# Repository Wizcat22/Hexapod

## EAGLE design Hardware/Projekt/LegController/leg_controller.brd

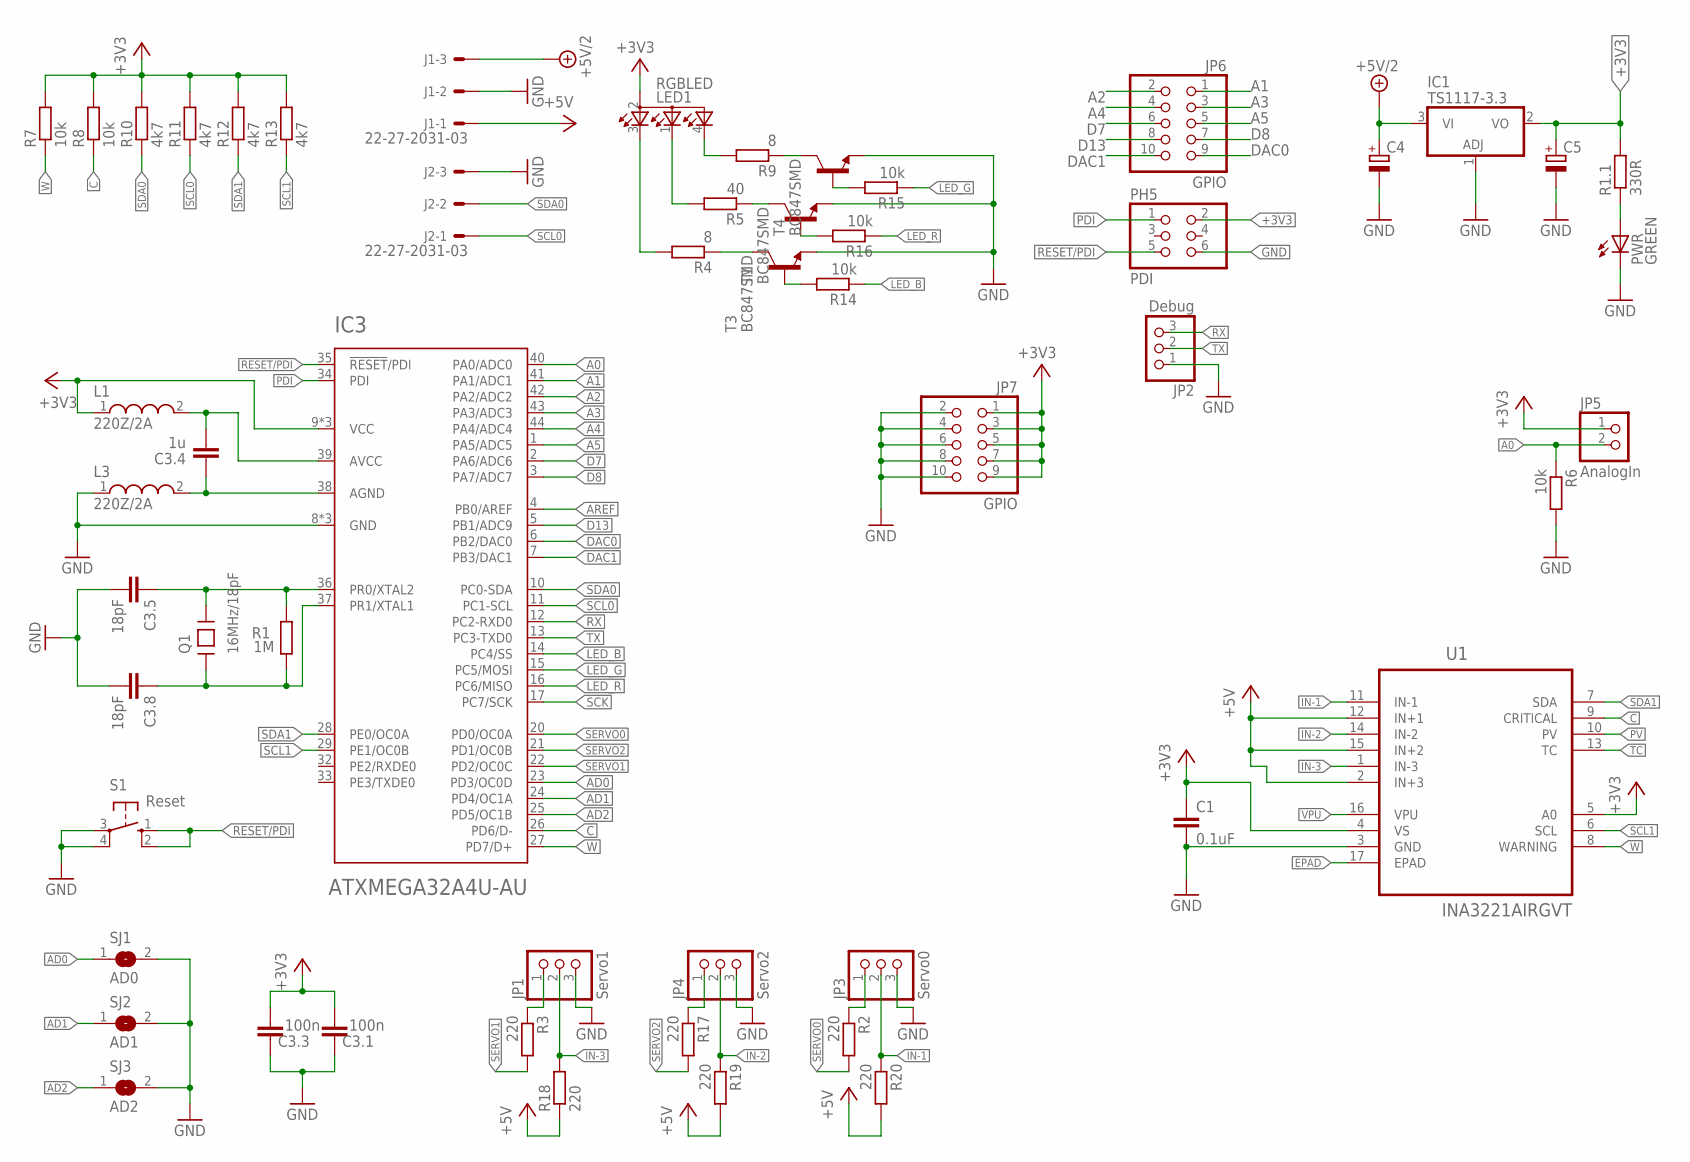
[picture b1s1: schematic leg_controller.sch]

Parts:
C1: 0.1uF; C0805
C3.1, C3.3: 100n; C0805K
C3.4: 1u; C0805K
C3.5, C3.8: 18pF; C0805K
C4, C5: CPOL-EUSMCA; SMC_A
IC1: TS1117-3.3; DPACK
IC3: ATXMEGA32A4U-AU; TQFP-44A-44
J1, J2: 22-27-2031-03; 6410-03
JP1: Servo1; 1X03
JP2: Debug; 1X03
JP3: Servo0; 1X03
JP4: Servo2; 1X03
JP5: AnalogIn; 1X02
JP6, JP7: GPIO; 2X05
L1, L3: 220Z/2A; WE-CBF_0805(W=3.0)
LED1: RGBLED; P-LCC4-RGB
PH5: PDI; 2X03
PWR: GREEN; CHIP-LED0805
Q1: 16MHz/18pF; CRYSTAL-ABRACON-ABM3-SMD
R1: 1M; R0805
R1.1: 330R; R0805
R2, R3, R17: 220; R0805
R4, R9: 8; R0805
R5: 40; R0805
R6: 10k; M0805
R7, R8, R14, R15, R16: 10k; R0805
R10, R11, R12, R13: 4k7; R0805
R18, R19, R20: 220; R1206
S1: Reset; B3F-10XX
SJ1: AD0; SJ
SJ2: AD1; SJ
SJ3: AD2; SJ
T1, T3, T4: BC847SMD; SOT23
U1: INA3221AIRGVT; QFN65P400X400X80-17N

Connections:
+3V3: C1.1, C3.1.1, C3.3.1, C5.+, IC1.2 (VO), IC3.9 (VCC), IC3.19 (VCC), IC3.31 (VCC), JP5.1, JP7.1, JP7.3, JP7.5, JP7.7, JP7.9, L1.1, LED1.2 (A2), PH5.2, R1.1.2, R7.2, R8.2, R10.2, R11.2, R12.2, R13.2, U1.4 (VS), U1.5 (A0)
+5V: J1.1, R18.1, R19.2, R20.2, U1.2 (IN+3), U1.12 (IN+1), U1.15 (IN+2)
+5V/2: C4.+, IC1.3 (VI), J1.3
A0: IC3.40 (PA0/ADC0), JP5.2, R6.1
A1: IC3.41 (PA1/ADC1), JP6.1
A2: IC3.42 (PA2/ADC2), JP6.2
A3: IC3.43 (PA3/ADC3), JP6.3
A4: IC3.44 (PA4/ADC4), JP6.4
A5: IC3.1 (PA5/ADC5), JP6.5
AD0: IC3.23 (PD3/OC0D), SJ1.1
AD1: IC3.24 (PD4/OC1A), SJ2.1
AD2: IC3.25 (PD5/OC1B), SJ3.1
AGND: C3.4.2, IC3.38 (AGND), L3.2
AREF: IC3.4 (PB0/AREF)
C: IC3.26 (PD6/D-), R8.1, U1.9 (CRITICAL)
D7: IC3.2 (PA6/ADC6), JP6.6
D8: IC3.3 (PA7/ADC7), JP6.7
D13: IC3.5 (PB1/ADC9), JP6.8
DAC0: IC3.6 (PB2/DAC0), JP6.9
DAC1: IC3.7 (PB3/DAC1), JP6.10
EPAD: U1.17 (EPAD)
GND: C1.2, C3.1.2, C3.3.2, C3.5.2, C3.8.2, C4.-, C5.-, IC1.1 (ADJ), IC3.8 (GND), IC3.18 (GND), IC3.30 (GND), J1.2, J2.3, JP1.3, JP2.1, JP3.3, JP4.3, JP7.2, JP7.4, JP7.6, JP7.8, JP7.10, L3.1, PH5.6, PWR.C, R6.2, S1.3, S1.4 (P1), SJ1.2, SJ2.2, SJ3.2, T1.2 (E), T3.2 (E), T4.2 (E), U1.3 (GND)
IN-1: JP3.2, R20.1, U1.11 (IN-1)
IN-2: JP4.2, R19.1, U1.14 (IN-2)
IN-3: JP1.2, R18.2, U1.1 (IN-3)
LED_B: IC3.14 (PC4/SS), R14.1
LED_G: IC3.15 (PC5/MOSI), R15.1
LED_R: IC3.16 (PC6/MISO), R16.1
unnamed: C3.4.1, IC3.39 (AVCC), L1.2
unnamed: R5.1, T1.3 (C)
unnamed: R4.1, T3.3 (C)
unnamed: R9.1, T4.3 (C)
unnamed: PWR.A, R1.1.1
unnamed: LED1.3 (CRED), R4.2
unnamed: JP3.1, R2.1
unnamed: JP1.1, R3.1
unnamed: LED1.1 (CBLUE), R5.2
unnamed: LED1.4 (CGREEN), R9.2
unnamed: JP4.1, R17.1
unnamed: R14.2, T3.1 (B)
unnamed: R15.2, T4.1 (B)
unnamed: R16.2, T1.1 (B)
PDI: IC3.34 (PDI), PH5.1
PV: U1.10 (PV)
RESET/PDI: IC3.35 (!RESET!/PDI), PH5.5, S1.1 (S), S1.2 (S1)
RX: IC3.12 (PC2-RXD0), JP2.3
SCK: IC3.17 (PC7/SCK)
SCL0: IC3.11 (PC1-SCL), J2.1, R11.1
SCL1: IC3.29 (PE1/OC0B), R13.1, U1.6 (SCL)
SDA0: IC3.10 (PC0-SDA), J2.2, R10.1
SDA1: IC3.28 (PE0/OC0A), R12.1, U1.7 (SDA)
SERVO0: IC3.20 (PD0/OC0A), R2.2
SERVO1: IC3.22 (PD2/OC0C), R3.2
SERVO2: IC3.21 (PD1/OC0B), R17.2
TC: U1.13 (TC)
TX: IC3.13 (PC3-TXD0), JP2.2
VPU: U1.16 (VPU)
W: IC3.27 (PD7/D+), R7.1, U1.8 (WARNING)
XTAL1R: C3.8.1, IC3.37 (PR1/XTAL1), Q1.P$1, R1.1
XTAL2: C3.5.1, IC3.36 (PR0/XTAL2), Q1.P$2, R1.2

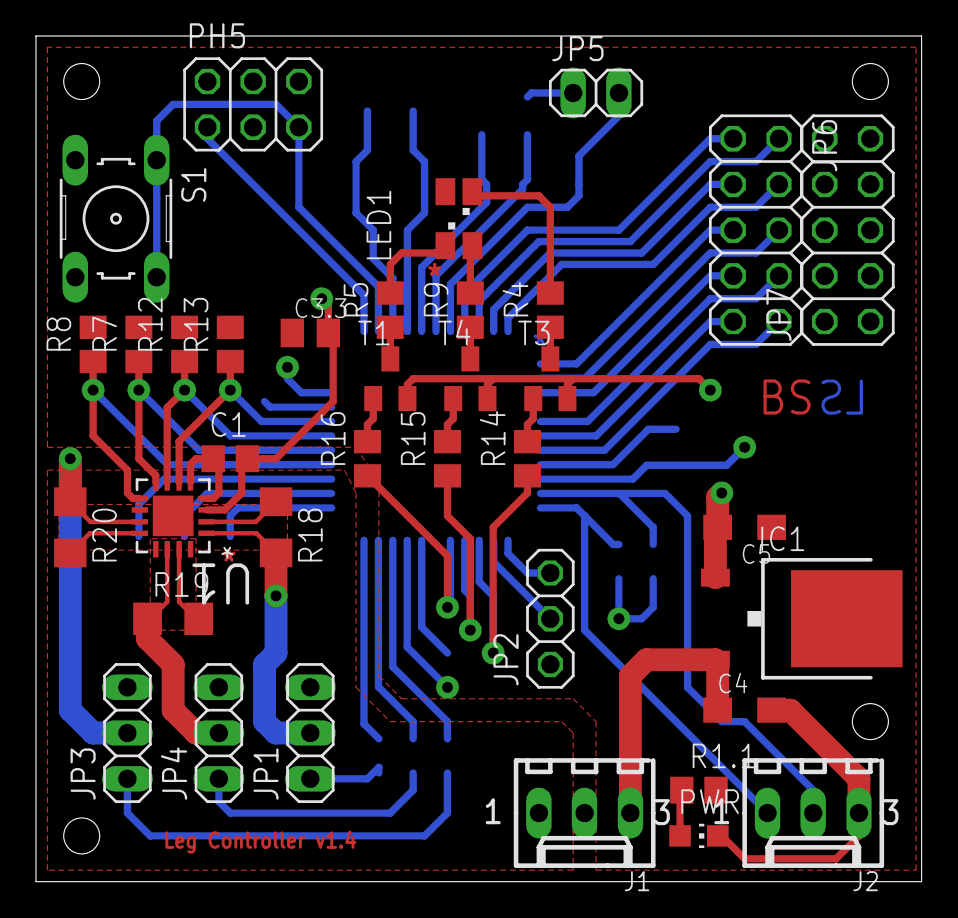
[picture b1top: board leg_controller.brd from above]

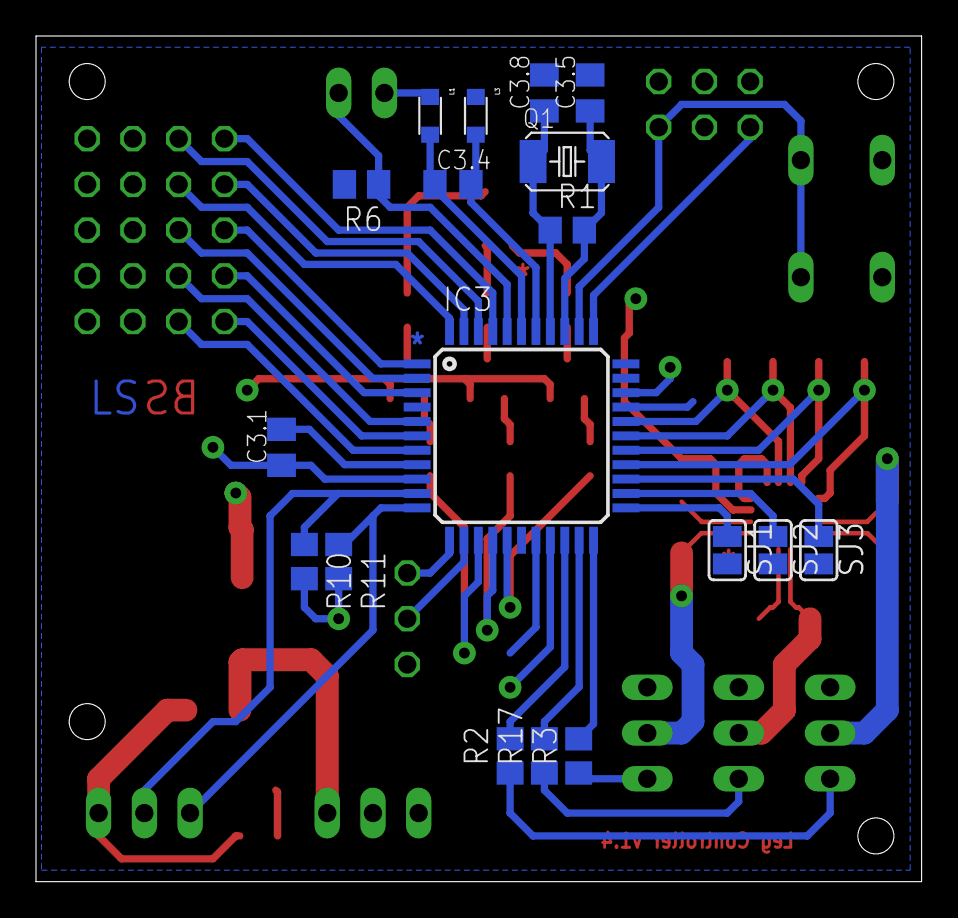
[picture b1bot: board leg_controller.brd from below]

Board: 2 copper layers, 49.2 x 47.0 mm, 54 parts (18 on the bottom side), 54 nets.

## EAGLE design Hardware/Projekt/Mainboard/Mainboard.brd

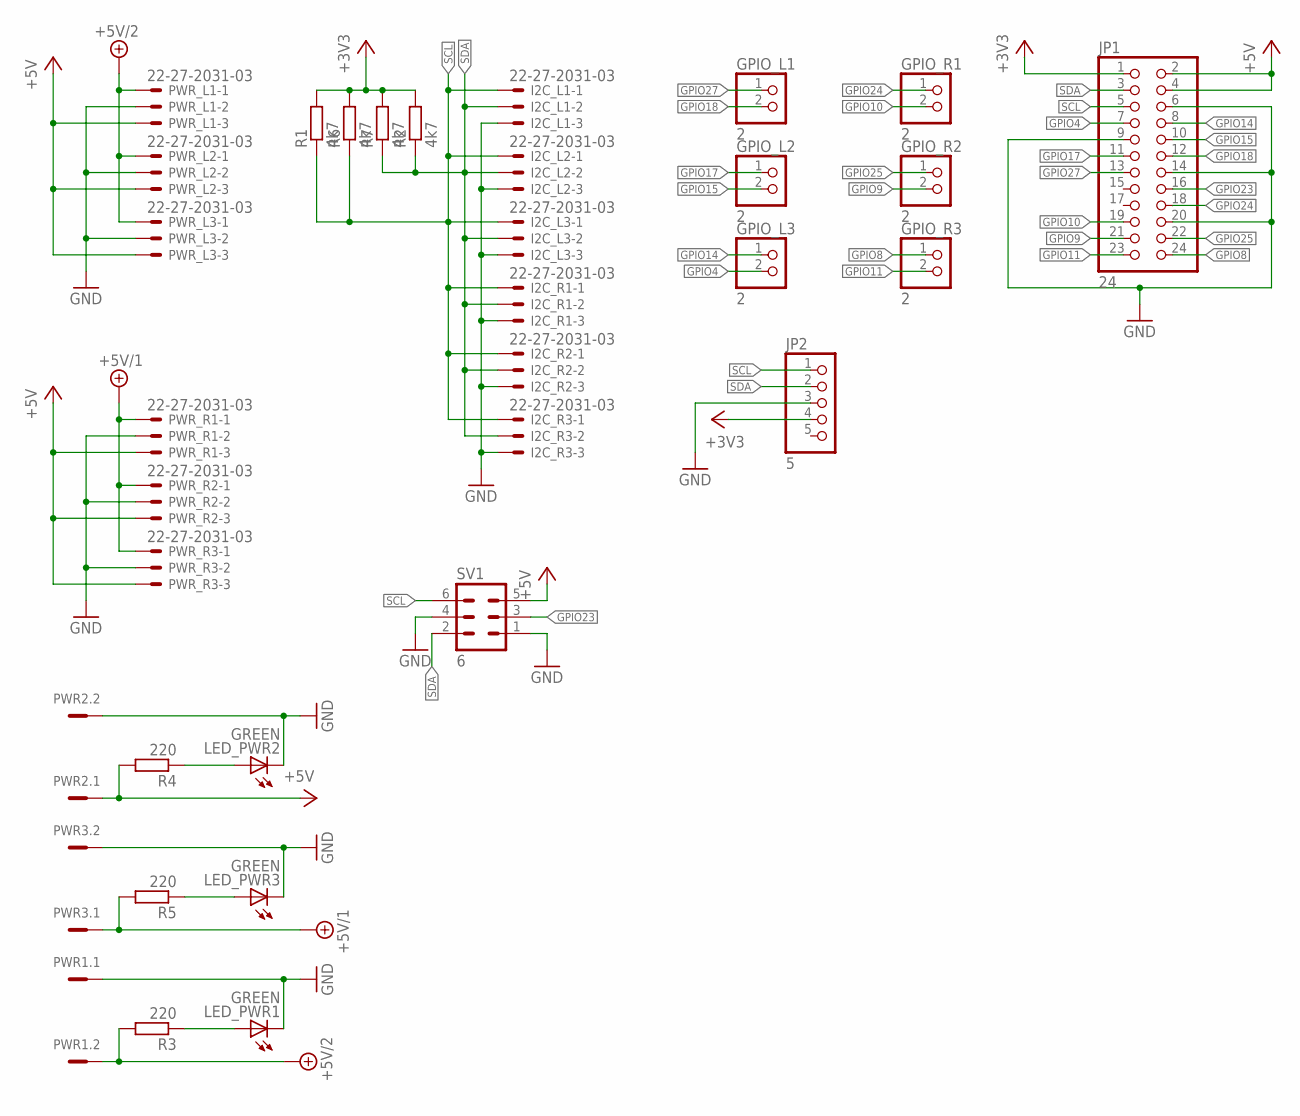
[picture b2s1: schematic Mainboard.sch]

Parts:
GPIO_L1, GPIO_L2, GPIO_L3: 2; 1X02
GPIO_R1, GPIO_R2, GPIO_R3: 2; 1X02
I2C_L1, I2C_L2, I2C_L3, I2C_R1, I2C_R2, I2C_R3: 22-27-2031-03; 6410-03
JP1: 24; 2X12
JP2: 5; 1X05
LED_PWR1, LED_PWR2, LED_PWR3: GREEN; CHIP-LED0805
PWR1, PWR2, PWR3: MCV2
PWR_L1, PWR_L2, PWR_L3: 22-27-2031-03; 6410-03
PWR_R1, PWR_R2, PWR_R3: 22-27-2031-03; 6410-03
R1, R2, R6, R7: 4k7; R0805
R3, R4, R5: 220; R0805
SV1: 6; ML6

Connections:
+3V3: JP1.1, JP2.4, R1.2, R2.2, R6.2, R7.2
+5V: JP1.2, JP1.4, PWR2.1, PWR_L1.3, PWR_L2.3, PWR_L3.3, PWR_R1.3, PWR_R2.3, PWR_R3.3, R4.2, SV1.5
+5V/1: PWR3.1, PWR_R1.1, PWR_R2.1, PWR_R3.1, R5.2
+5V/2: PWR1.2, PWR_L1.1, PWR_L2.1, PWR_L3.1, R3.2
GND: I2C_L1.3, I2C_L2.3, I2C_L3.3, I2C_R1.3, I2C_R2.3, I2C_R3.3, JP1.6, JP1.9, JP1.14, JP1.20, JP2.3, LED_PWR1.C, LED_PWR2.C, LED_PWR3.C, PWR1.1, PWR2.2, PWR3.2, PWR_L1.2, PWR_L2.2, PWR_L3.2, PWR_R1.2, PWR_R2.2, PWR_R3.2, SV1.1, SV1.4
GPIO4: GPIO_L3.2, JP1.7
GPIO8: GPIO_R3.1, JP1.24
GPIO9: GPIO_R2.2, JP1.21
GPIO10: GPIO_R1.2, JP1.19
GPIO11: GPIO_R3.2, JP1.23
GPIO14: GPIO_L3.1, JP1.8
GPIO15: GPIO_L2.2, JP1.10
GPIO17: GPIO_L2.1, JP1.11
GPIO18: GPIO_L1.2, JP1.12
GPIO23: JP1.16, SV1.3
GPIO24: GPIO_R1.1, JP1.18
GPIO25: GPIO_R2.1, JP1.22
GPIO27: GPIO_L1.1, JP1.13
unnamed: LED_PWR1.A, R3.1
unnamed: LED_PWR2.A, R4.1
unnamed: LED_PWR3.A, R5.1
SCL: I2C_L1.1, I2C_L2.1, I2C_L3.1, I2C_R1.1, I2C_R2.1, I2C_R3.1, JP1.5, JP2.1, R1.1, R6.1, SV1.6
SDA: I2C_L1.2, I2C_L2.2, I2C_L3.2, I2C_R1.2, I2C_R2.2, I2C_R3.2, JP1.3, JP2.2, R2.1, R7.1, SV1.2

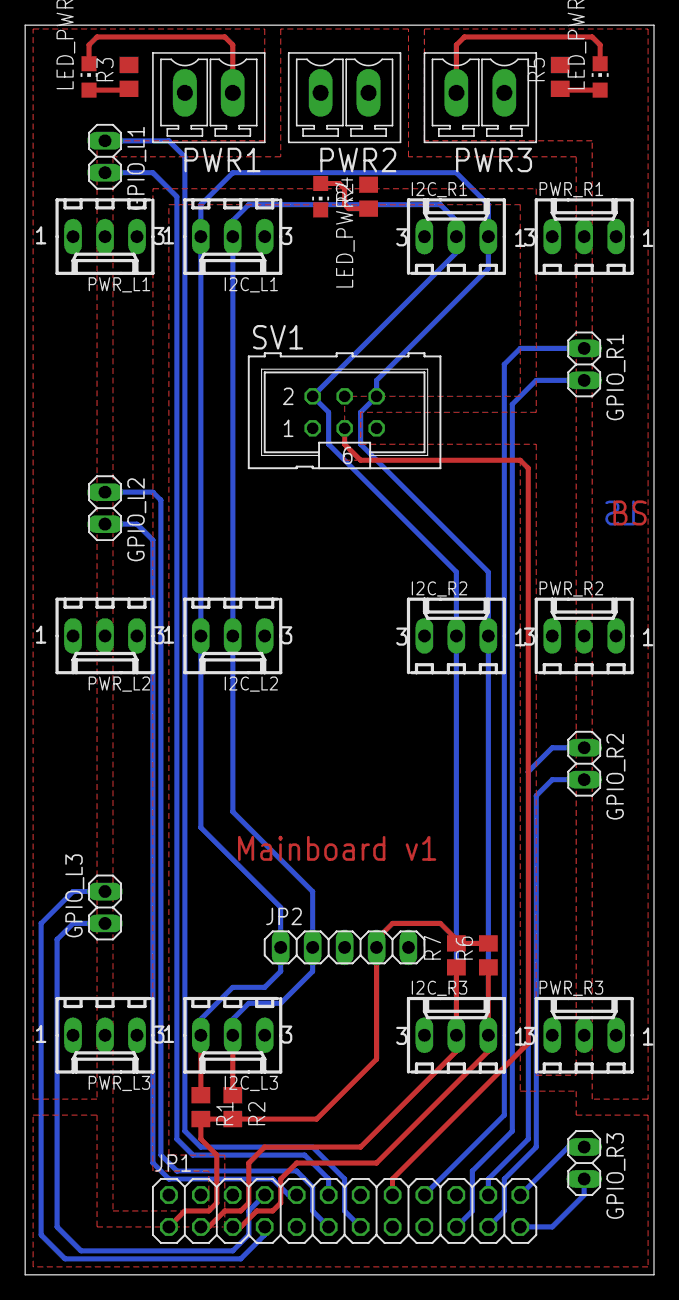
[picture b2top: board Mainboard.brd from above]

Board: 2 copper layers, 50.0 x 99.4 mm, 34 parts (0 on the bottom side), 23 nets.

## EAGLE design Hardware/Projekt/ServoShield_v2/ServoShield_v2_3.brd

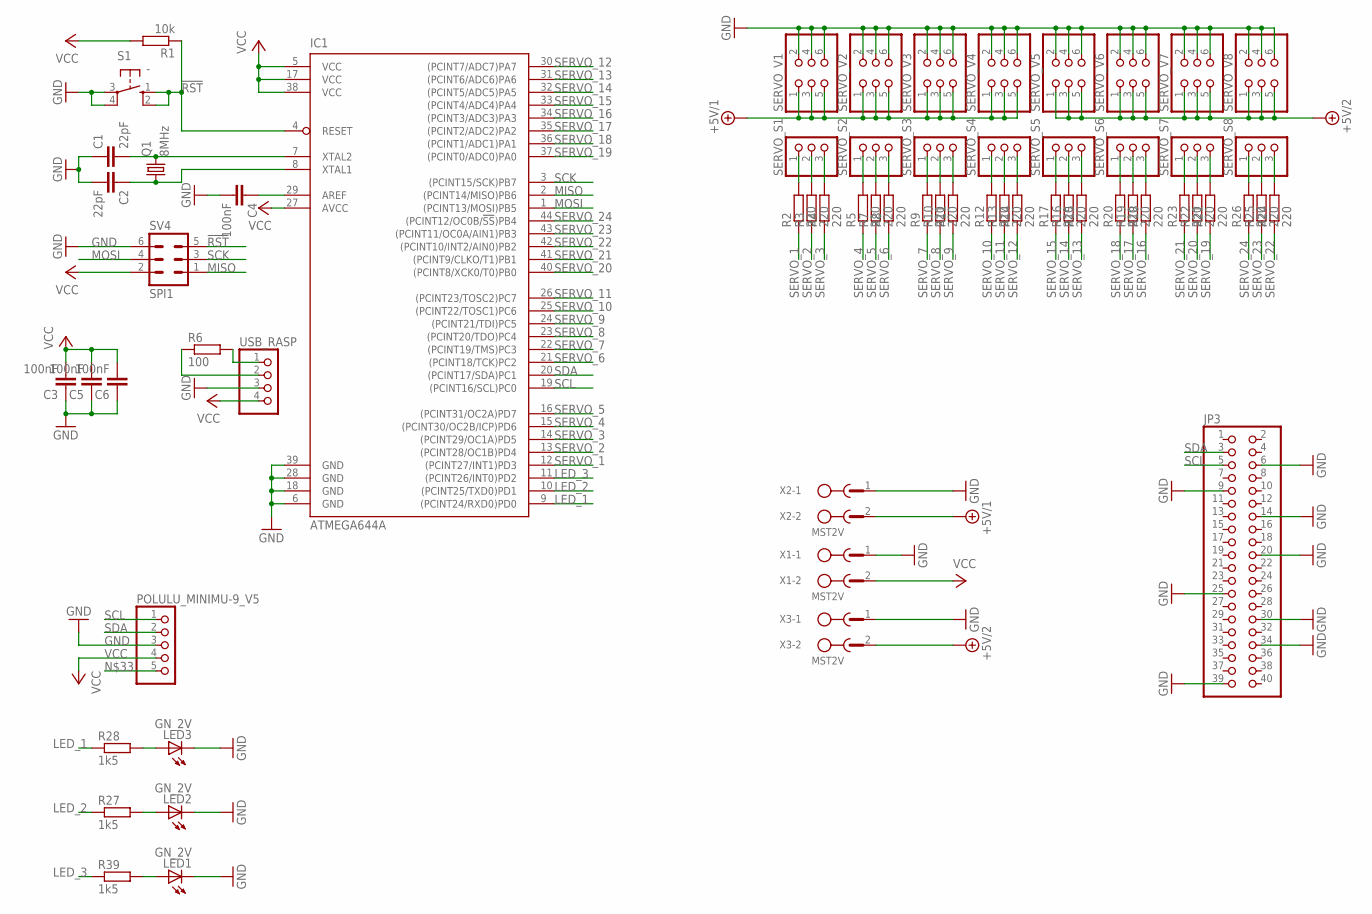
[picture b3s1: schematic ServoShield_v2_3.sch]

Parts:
C1, C2: 22pF; C0805
C3, C4, C5, C6: 100nF; C0805
IC1: ATMEGA644A; TQFP44
JP3: PINHD-2X20; 2X20
LED1, LED2, LED3: GN_2V; LED3MM
POLULU_MINIMU-9_V5: PINHD-1X5; 1X05
Q1: 8MHz; CTS406
R1: 10k; R0805
R2, R3, R4, R5, R7, R8, R9, R10, R11, R12, R13, R14, R15, R16, R17, R18, R19, R20, R21, R22, R23, R24, R25, R26: 220; R0805
R6: 100; R0805
R27, R28, R39: 1k5; R0805
S1: -; B3F-10XX
SERVO_S1, SERVO_S2, SERVO_S3, SERVO_S4, SERVO_S5, SERVO_S6, SERVO_S7, SERVO_S8: PINHD-1X3; 1X03
SERVO_V1, SERVO_V2, SERVO_V3, SERVO_V4, SERVO_V5, SERVO_V6, SERVO_V7, SERVO_V8: PINHD-2X3; 2X03
SV4: SPI1; ML6
USB_RASP: PINHD-1X4; 1X04
X1, X2, X3: MST2V; MSTBV2

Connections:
!RST: IC1.4 (RESET), R1.1, S1.1 (S), S1.2 (S1), SV4.5
+5V/1: SERVO_V1.1, SERVO_V1.3, SERVO_V1.5, SERVO_V2.1, SERVO_V2.3, SERVO_V2.5, SERVO_V3.1, SERVO_V3.3, SERVO_V3.5, SERVO_V4.1, SERVO_V4.3, SERVO_V4.5, X2.2; also elsewhere on the board
+5V/2: SERVO_V5.1, SERVO_V5.3, SERVO_V5.5, SERVO_V6.1, SERVO_V6.3, SERVO_V6.5, SERVO_V7.1, SERVO_V7.3, SERVO_V7.5, SERVO_V8.1, SERVO_V8.3, SERVO_V8.5, X3.2; also elsewhere on the board
GND: C1.1, C2.2, C3.1, C4.2, C5.1, C6.1, IC1.6 (GND), IC1.18 (GND), IC1.28 (GND), IC1.39 (GND), JP3.6, JP3.9, JP3.14, JP3.20, JP3.25, JP3.30, JP3.34, JP3.39, LED1.K (C), LED2.K (C), LED3.K (C), POLULU_MINIMU-9_V5.3, S1.3, S1.4 (P1), SERVO_V1.2, SERVO_V1.4, SERVO_V1.6, SERVO_V2.2, SERVO_V2.4, SERVO_V2.6, SERVO_V3.2, SERVO_V3.4, SERVO_V3.6, SERVO_V4.2, SERVO_V4.4, SERVO_V4.6, SERVO_V5.2, SERVO_V5.4, SERVO_V5.6, SERVO_V6.2, SERVO_V6.4, SERVO_V6.6, SERVO_V7.2, SERVO_V7.4, SERVO_V7.6, SERVO_V8.2, SERVO_V8.4, SERVO_V8.6, SV4.6, USB_RASP.3, X1.1, X2.1, X3.1; also elsewhere on the board
LED_1: IC1.9 ((PCINT24/RXD0)PD0), R28.1
LED_2: IC1.10 ((PCINT25/TXD0)PD1), R27.1
LED_3: IC1.11 ((PCINT26/INT0)PD2), R39.1
MISO: IC1.2 ((PCINT14/MISO)PB6), SV4.1
MOSI: IC1.1 ((PCINT13/MOSI)PB5), SV4.4
unnamed 9: C2.1, IC1.8 (XTAL1), Q1.1; also elsewhere on the board
unnamed 10: C1.2, IC1.7 (XTAL2), Q1.3 (2); also elsewhere on the board
unnamed: R2.2, SERVO_S1.1
unnamed: R3.2, SERVO_S1.2
unnamed: R4.2, SERVO_S1.3
unnamed: R5.2, SERVO_S2.1
unnamed: R7.2, SERVO_S2.2
unnamed: R8.2, SERVO_S2.3
unnamed: R9.2, SERVO_S3.1
unnamed: R10.2, SERVO_S3.2
unnamed: R11.2, SERVO_S3.3
unnamed: R12.2, SERVO_S4.1
unnamed: R13.2, SERVO_S4.2
unnamed: R14.2, SERVO_S4.3
unnamed: R17.2, SERVO_S5.1
unnamed: R16.2, SERVO_S5.2
unnamed: R15.2, SERVO_S5.3
unnamed: R20.2, SERVO_S6.1
unnamed: R19.2, SERVO_S6.2
unnamed: R18.2, SERVO_S6.3
unnamed: R23.2, SERVO_S7.1
unnamed: R22.2, SERVO_S7.2
unnamed: R21.2, SERVO_S7.3
unnamed: R26.2, SERVO_S8.1
unnamed: R25.2, SERVO_S8.2
unnamed: R24.2, SERVO_S8.3
unnamed: LED2.A, R27.2
unnamed: LED3.A, R28.2
unnamed: R6.2, USB_RASP.1
unnamed: C4.1, IC1.29 (AREF)
unnamed: LED1.A, R39.2
unnamed: R6.1, USB_RASP.2
SCK: IC1.3 ((PCINT15/SCK)PB7), SV4.3
SCL: IC1.19 ((PCINT16/SCL)PC0), JP3.5, POLULU_MINIMU-9_V5.1
SDA: IC1.20 ((PCINT17/SDA)PC1), JP3.3, POLULU_MINIMU-9_V5.2
SERVO_1: IC1.12 ((PCINT27/INT1)PD3), R2.1
SERVO_2: IC1.13 ((PCINT28/OC1B)PD4), R3.1
SERVO_3: IC1.14 ((PCINT29/OC1A)PD5), R4.1
SERVO_4: IC1.15 ((PCINT30/OC2B/ICP)PD6), R5.1
SERVO_5: IC1.16 ((PCINT31/OC2A)PD7), R7.1
SERVO_6: IC1.21 ((PCINT18/TCK)PC2), R8.1
SERVO_7: IC1.22 ((PCINT19/TMS)PC3), R9.1
SERVO_8: IC1.23 ((PCINT20/TDO)PC4), R10.1
SERVO_9: IC1.24 ((PCINT21/TDI)PC5), R11.1
SERVO_10: IC1.25 ((PCINT22/TOSC1)PC6), R12.1
SERVO_11: IC1.26 ((PCINT23/TOSC2)PC7), R13.1
SERVO_12: IC1.30 ((PCINT7/ADC7)PA7), R14.1
SERVO_13: IC1.31 ((PCINT6/ADC6)PA6), R15.1
SERVO_14: IC1.32 ((PCINT5/ADC5)PA5), R16.1
SERVO_15: IC1.33 ((PCINT4/ADC4)PA4), R17.1
SERVO_16: IC1.34 ((PCINT3/ADC3)PA3), R18.1
SERVO_17: IC1.35 ((PCINT2/ADC2)PA2), R19.1
SERVO_18: IC1.36 ((PCINT1/ADC1)PA1), R20.1
SERVO_19: IC1.37 ((PCINT0/ADC0)PA0), R21.1
SERVO_20: IC1.40 ((PCINT8/XCK0/T0)PB0), R22.1
SERVO_21: IC1.41 ((PCINT9/CLKO/T1)PB1), R23.1
SERVO_22: IC1.42 ((PCINT10/INT2/AIN0)PB2), R24.1
SERVO_23: IC1.43 ((PCINT11/OC0A/AIN1)PB3), R25.1
SERVO_24: IC1.44 ((PCINT12/OC0B/!SS!)PB4), R26.1
VCC: C3.2, C5.2, C6.2, IC1.5 (VCC), IC1.17 (VCC), IC1.27 (AVCC), IC1.38 (VCC), POLULU_MINIMU-9_V5.4, R1.2, SV4.2, USB_RASP.4, X1.2; also elsewhere on the board
VDD: JP3.1, POLULU_MINIMU-9_V5.5

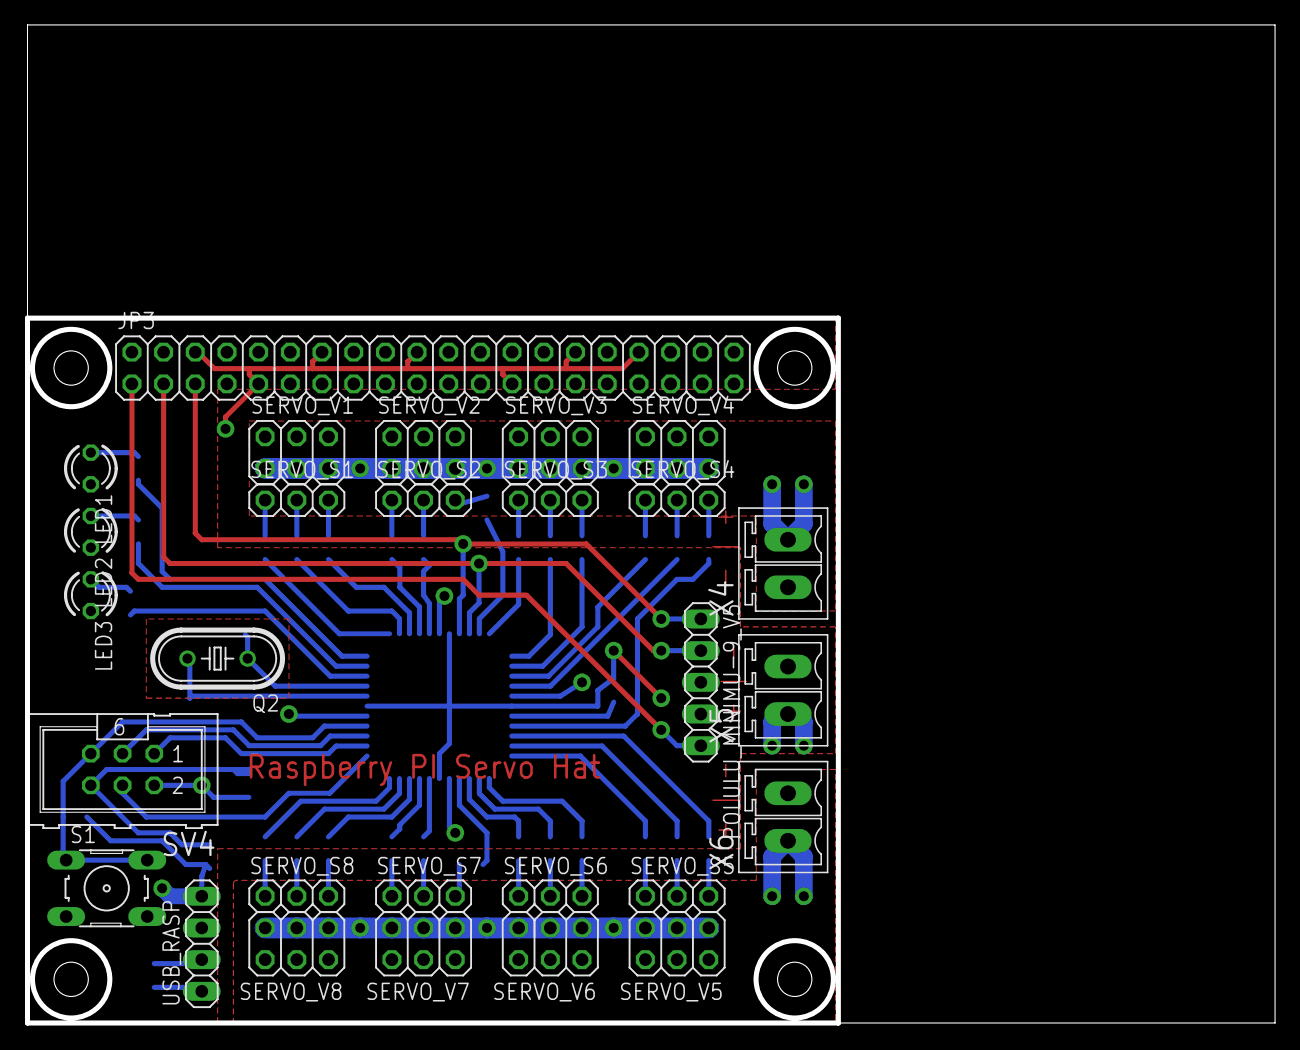
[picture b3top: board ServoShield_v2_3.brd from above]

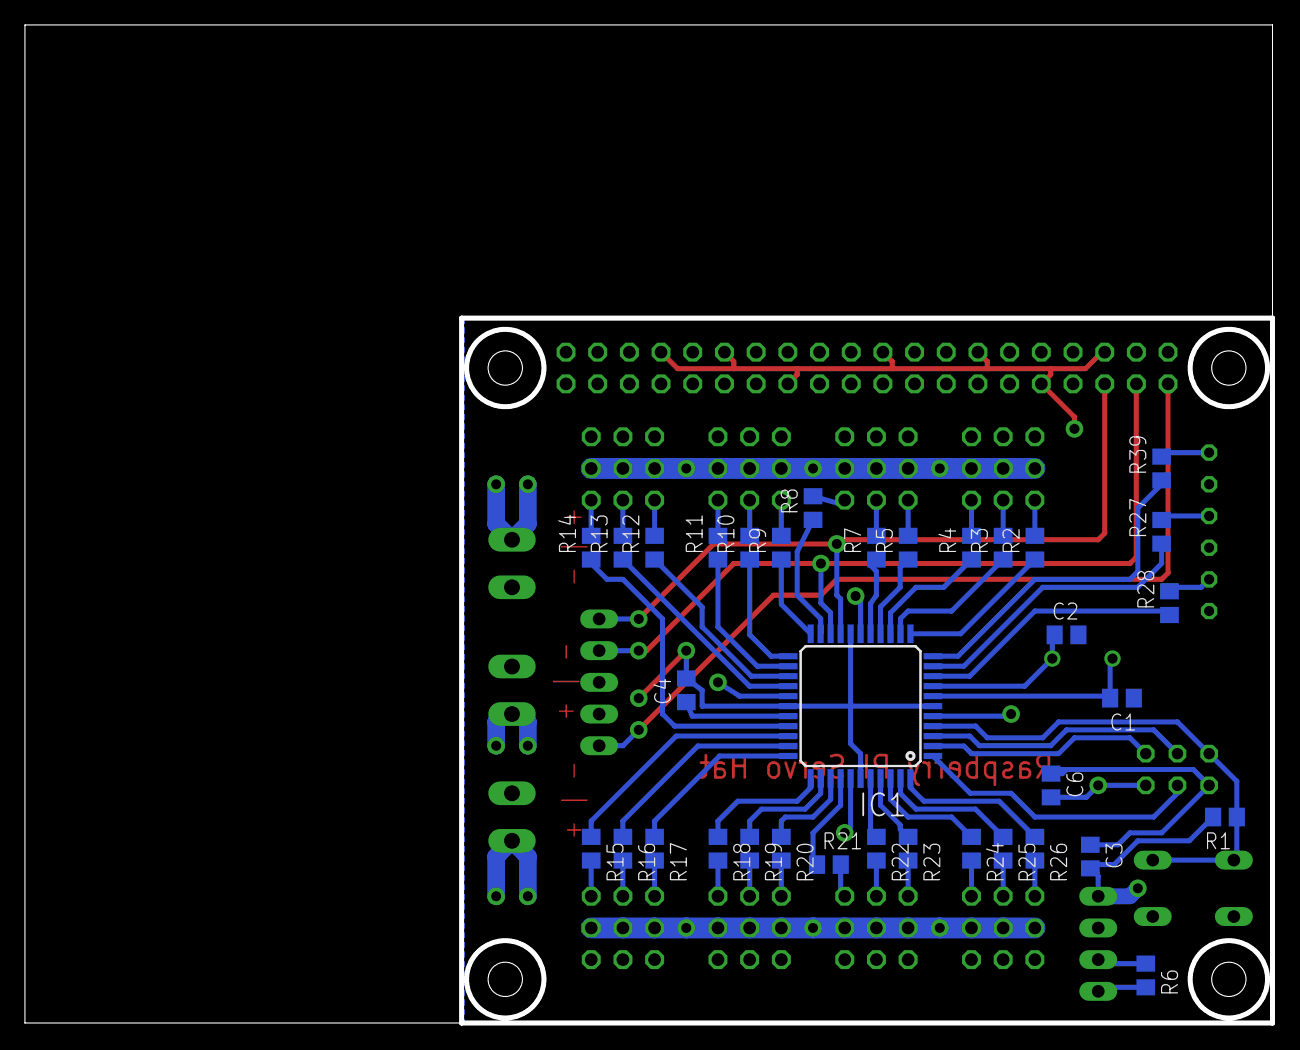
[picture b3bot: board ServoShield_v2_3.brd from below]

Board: 2 copper layers, 100.0 x 80.0 mm, 63 parts (35 on the bottom side), 70 nets.

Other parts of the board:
Q2: 8MHz; HC49U-V
X4, X5, X6: MCV2

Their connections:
+5V/1: X4.2; also elsewhere on the board
+5V/2: X6.1; also elsewhere on the board
GND: X4.1, X5.2, X6.2; also elsewhere on the board
unnamed 9: Q2.1; also elsewhere on the board
unnamed 10: Q2.2; also elsewhere on the board
VCC: X5.1; also elsewhere on the board

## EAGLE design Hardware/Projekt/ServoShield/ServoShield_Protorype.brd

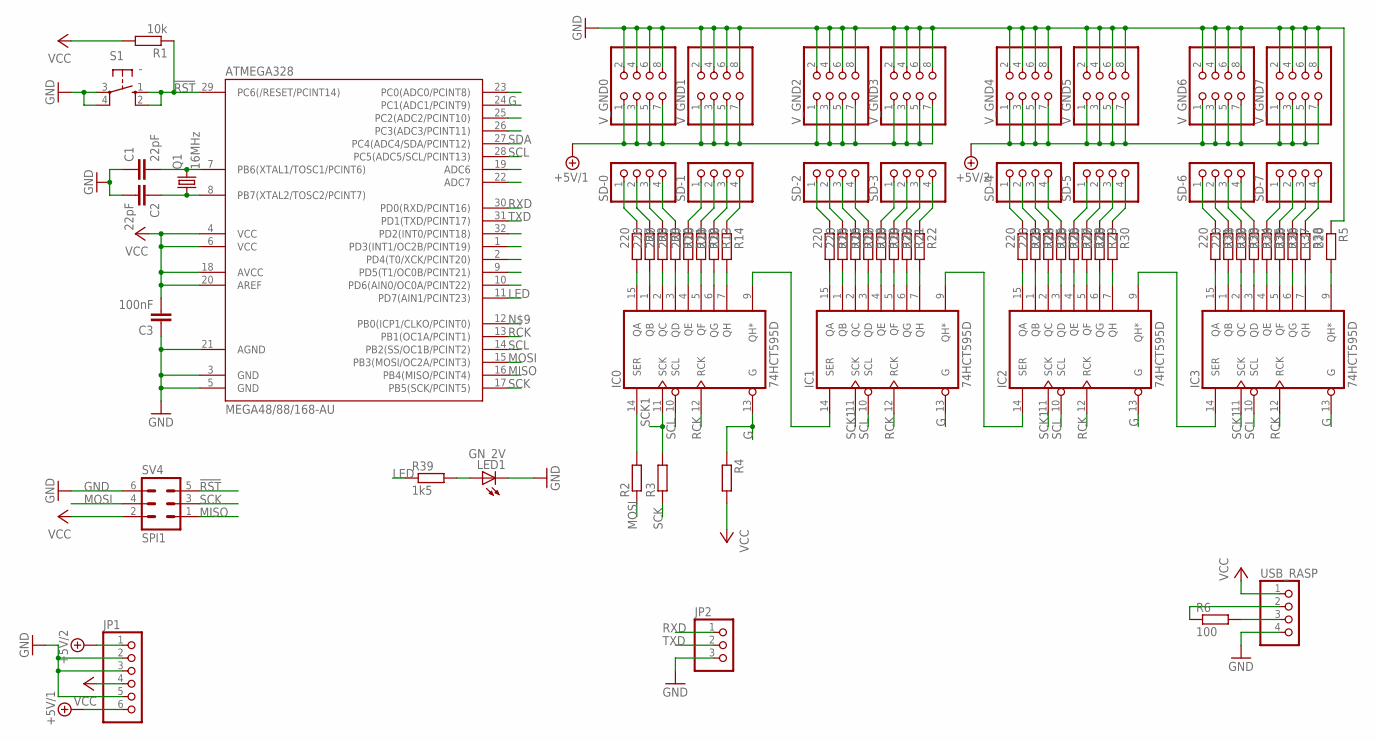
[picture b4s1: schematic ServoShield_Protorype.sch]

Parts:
ATMEGA328: MEGA48/88/168-AU; TQFP32-08
C1, C2: 22pF; C0805
C3: 100nF; C0805
IC0, IC1, IC2, IC3: 74HCT595D; SO16
JP1: PINHD-1X6; 1X06
JP2: PINHD-1X3; 1X03
LED1: GN_2V; LED3MM
Q1: 16MHz; HC49UP
R1: 10k; R0805
R2, R3, R4: R-EU_R0805; R0805
R5, R7, R8, R9, R10, R11, R12, R13, R14, R15, R16, R17, R18, R19, R20, R21, R22, R23, R24, R25, R26, R27, R28, R29, R30, R31, R32, R33, R34, R35, R36, R37, R38: 220; R0805
R6: 100; R0805
R39: 1k5; R0805
S1: -; B3F-10XX
SD-0, SD-1, SD-2, SD-3, SD-4, SD-5, SD-6, SD-7: PINHD-1X4; 1X04
SV4: SPI1; ML6
USB_RASP: PINHD-1X4; 1X04
V_GND0, V_GND1, V_GND2, V_GND3, V_GND4, V_GND5, V_GND6, V_GND7: PINHD-2X4; 2X04

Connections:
!RST: ATMEGA328.29 (PC6(/RESET/PCINT14)), R1.1, S1.1 (S), S1.2 (S1), SV4.5
+5V/1: JP1.6, V_GND0.1, V_GND0.3, V_GND0.5, V_GND0.7, V_GND1.1, V_GND1.3, V_GND1.5, V_GND1.7, V_GND2.1, V_GND2.3, V_GND2.5, V_GND2.7, V_GND3.1, V_GND3.3, V_GND3.5, V_GND3.7
+5V/2: JP1.1, V_GND4.1, V_GND4.3, V_GND4.5, V_GND4.7, V_GND5.1, V_GND5.3, V_GND5.5, V_GND5.7, V_GND6.1, V_GND6.3, V_GND6.5, V_GND6.7, V_GND7.1, V_GND7.3, V_GND7.5, V_GND7.7
G: ATMEGA328.24 (PC1(ADC1/PCINT9)), IC0.13 (G), IC1.13 (G), IC2.13 (G), IC3.13 (G), R4.1
GND: ATMEGA328.3 (GND), ATMEGA328.5 (GND), ATMEGA328.21 (AGND), C1.1, C2.2, C3.1, IC0.8 (GND), IC1.8 (GND), IC2.8 (GND), IC3.8 (GND), JP1.2, JP1.3, JP1.5, JP2.3, LED1.K (C), R5.1, S1.3, S1.4 (P1), SV4.6, USB_RASP.4, V_GND0.2, V_GND0.4, V_GND0.6, V_GND0.8, V_GND1.2, V_GND1.4, V_GND1.6, V_GND1.8, V_GND2.2, V_GND2.4, V_GND2.6, V_GND2.8, V_GND3.2, V_GND3.4, V_GND3.6, V_GND3.8, V_GND4.2, V_GND4.4, V_GND4.6, V_GND4.8, V_GND5.2, V_GND5.4, V_GND5.6, V_GND5.8, V_GND6.2, V_GND6.4, V_GND6.6, V_GND6.8, V_GND7.2, V_GND7.4, V_GND7.6, V_GND7.8
LED: ATMEGA328.11 (PD7(AIN1/PCINT23)), R39.1
MISO: ATMEGA328.16 (PB4(MISO/PCINT4)), SV4.1
MOSI: ATMEGA328.15 (PB3(MOSI/OC2A/PCINT3)), R2.1, SV4.4
unnamed: ATMEGA328.8 (PB7(XTAL2/TOSC2/PCINT7)), C2.1, Q1.1
unnamed: ATMEGA328.7 (PB6(XTAL1/TOSC1/PCINT6)), C1.2, Q1.2
unnamed: IC0.15 (QA), R7.2
unnamed: IC0.14 (SER), R2.2
unnamed: IC1.9 (QH*), IC2.14 (SER)
unnamed: IC0.1 (QB), R8.2
unnamed: IC0.2 (QC), R9.2
unnamed: IC0.3 (QD), R10.2
unnamed: IC0.4 (QE), R11.2
unnamed: IC0.5 (QF), R12.2
unnamed: IC0.6 (QG), R13.2
unnamed: IC0.7 (QH), R14.2
unnamed: R7.1, SD-0.1
unnamed: R8.1, SD-0.2
unnamed: R9.1, SD-0.3
unnamed: R10.1, SD-0.4
unnamed: R11.1, SD-1.1
unnamed: R12.1, SD-1.2
unnamed: R13.1, SD-1.3
unnamed: R14.1, SD-1.4
unnamed: IC1.15 (QA), R15.2
unnamed: R15.1, SD-2.1
unnamed: IC1.1 (QB), R16.2
unnamed: IC0.9 (QH*), IC1.14 (SER)
unnamed: IC1.2 (QC), R17.2
unnamed: IC1.3 (QD), R18.2
unnamed: IC1.4 (QE), R19.2
unnamed: IC1.5 (QF), R20.2
unnamed: IC1.6 (QG), R21.2
unnamed: IC1.7 (QH), R22.2
unnamed: R16.1, SD-2.2
unnamed: R17.1, SD-2.3
unnamed: R18.1, SD-2.4
unnamed: R19.1, SD-3.1
unnamed: R20.1, SD-3.2
unnamed: R21.1, SD-3.3
unnamed: R22.1, SD-3.4
unnamed: IC2.15 (QA), R23.2
unnamed: IC2.1 (QB), R24.2
unnamed: IC3.9 (QH*), R5.2
unnamed: IC2.9 (QH*), IC3.14 (SER)
unnamed: IC2.2 (QC), R25.2
unnamed: IC2.3 (QD), R26.2
unnamed: IC2.4 (QE), R27.2
unnamed: IC2.5 (QF), R28.2
unnamed: IC2.6 (QG), R29.2
unnamed: IC2.7 (QH), R30.2
unnamed: R23.1, SD-4.1
unnamed: R24.1, SD-4.2
unnamed: R25.1, SD-4.3
unnamed: R26.1, SD-4.4
unnamed: R27.1, SD-5.1
unnamed: R28.1, SD-5.2
unnamed: R29.1, SD-5.3
unnamed: R30.1, SD-5.4
unnamed: IC3.15 (QA), R31.2
unnamed: IC3.1 (QB), R32.2
unnamed: IC3.2 (QC), R33.2
unnamed: IC3.3 (QD), R34.2
unnamed: IC3.4 (QE), R35.2
unnamed: IC3.5 (QF), R36.2
unnamed: IC3.6 (QG), R37.2
unnamed: IC3.7 (QH), R38.2
unnamed: R31.1, SD-6.1
unnamed: R32.1, SD-6.2
unnamed: R33.1, SD-6.3
unnamed: R34.1, SD-6.4
unnamed: R35.1, SD-7.1
unnamed: R36.1, SD-7.2
unnamed: R37.1, SD-7.3
unnamed: R38.1, SD-7.4
unnamed: R6.2, USB_RASP.3
unnamed: LED1.A, R39.2
unnamed: R6.1, USB_RASP.2
RCK: ATMEGA328.13 (PB1(OC1A/PCINT1)), IC0.12 (RCK), IC1.12 (RCK), IC2.12 (RCK), IC3.12 (RCK)
RXD: ATMEGA328.30 (PD0(RXD/PCINT16)), JP2.1
SCK: ATMEGA328.17 (PB5(SCK/PCINT5)), R3.1, SV4.3
SCK1: IC0.11 (SCK), IC1.11 (SCK), IC2.11 (SCK), IC3.11 (SCK), R3.2
SCL: ATMEGA328.14 (PB2(SS/OC1B/PCINT2)), ATMEGA328.28 (PC5(ADC5/SCL/PCINT13)), IC0.10 (SCL), IC1.10 (SCL), IC2.10 (SCL), IC3.10 (SCL)
SDA: ATMEGA328.27 (PC4(ADC4/SDA/PCINT12))
TXD: ATMEGA328.31 (PD1(TXD/PCINT17)), JP2.2
VCC: ATMEGA328.4 (VCC), ATMEGA328.6 (VCC), ATMEGA328.18 (AVCC), ATMEGA328.20 (AREF), C3.2, IC0.16 (VCC), IC1.16 (VCC), IC2.16 (VCC), IC3.16 (VCC), JP1.4, R1.2, R4.2, SV4.2, USB_RASP.1

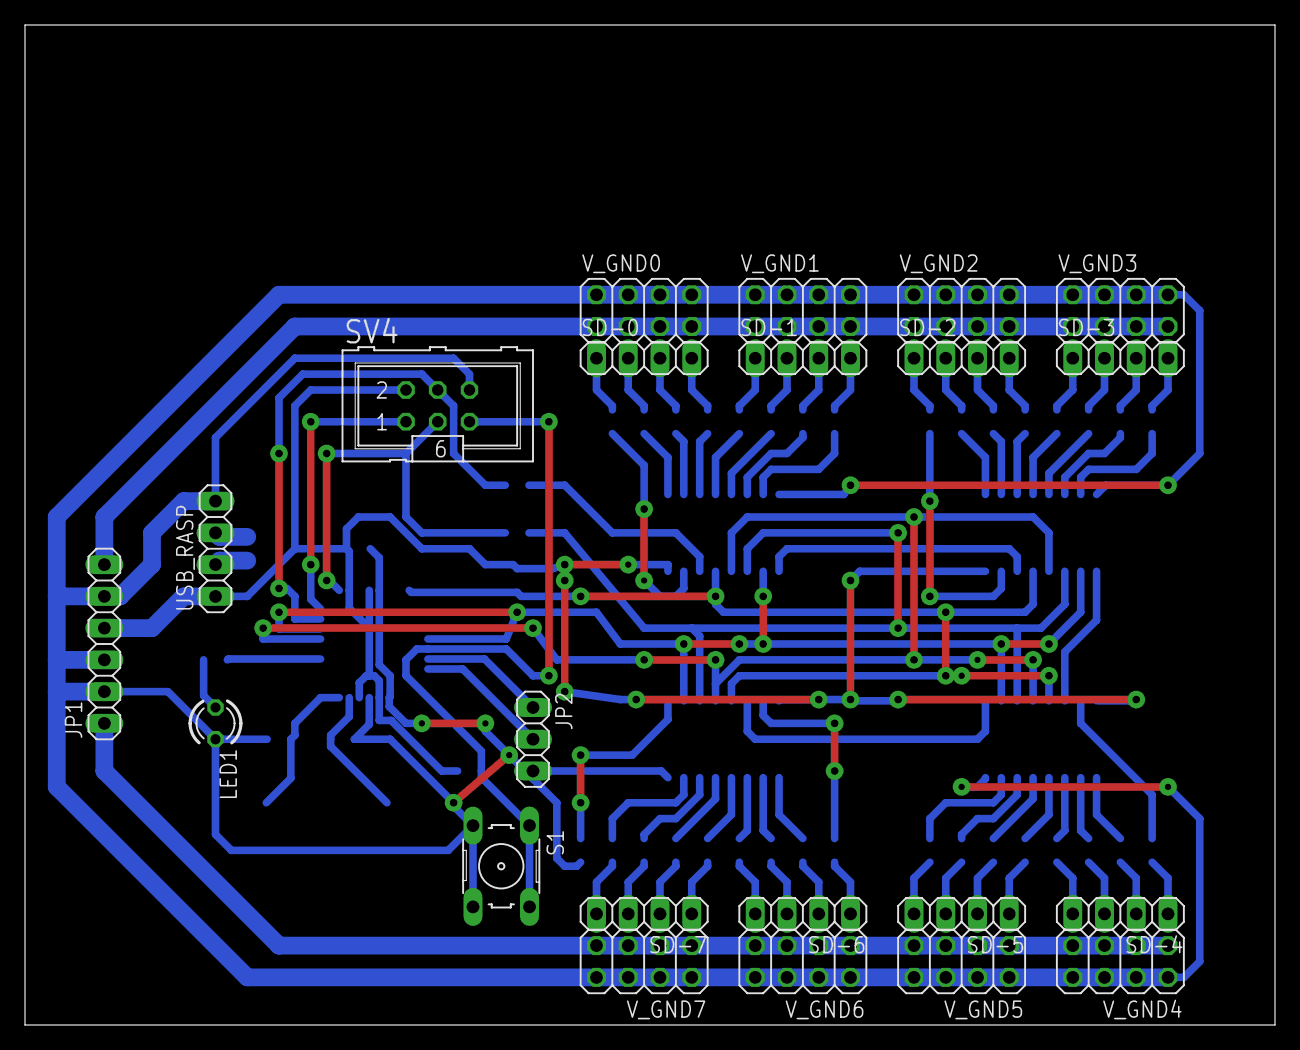
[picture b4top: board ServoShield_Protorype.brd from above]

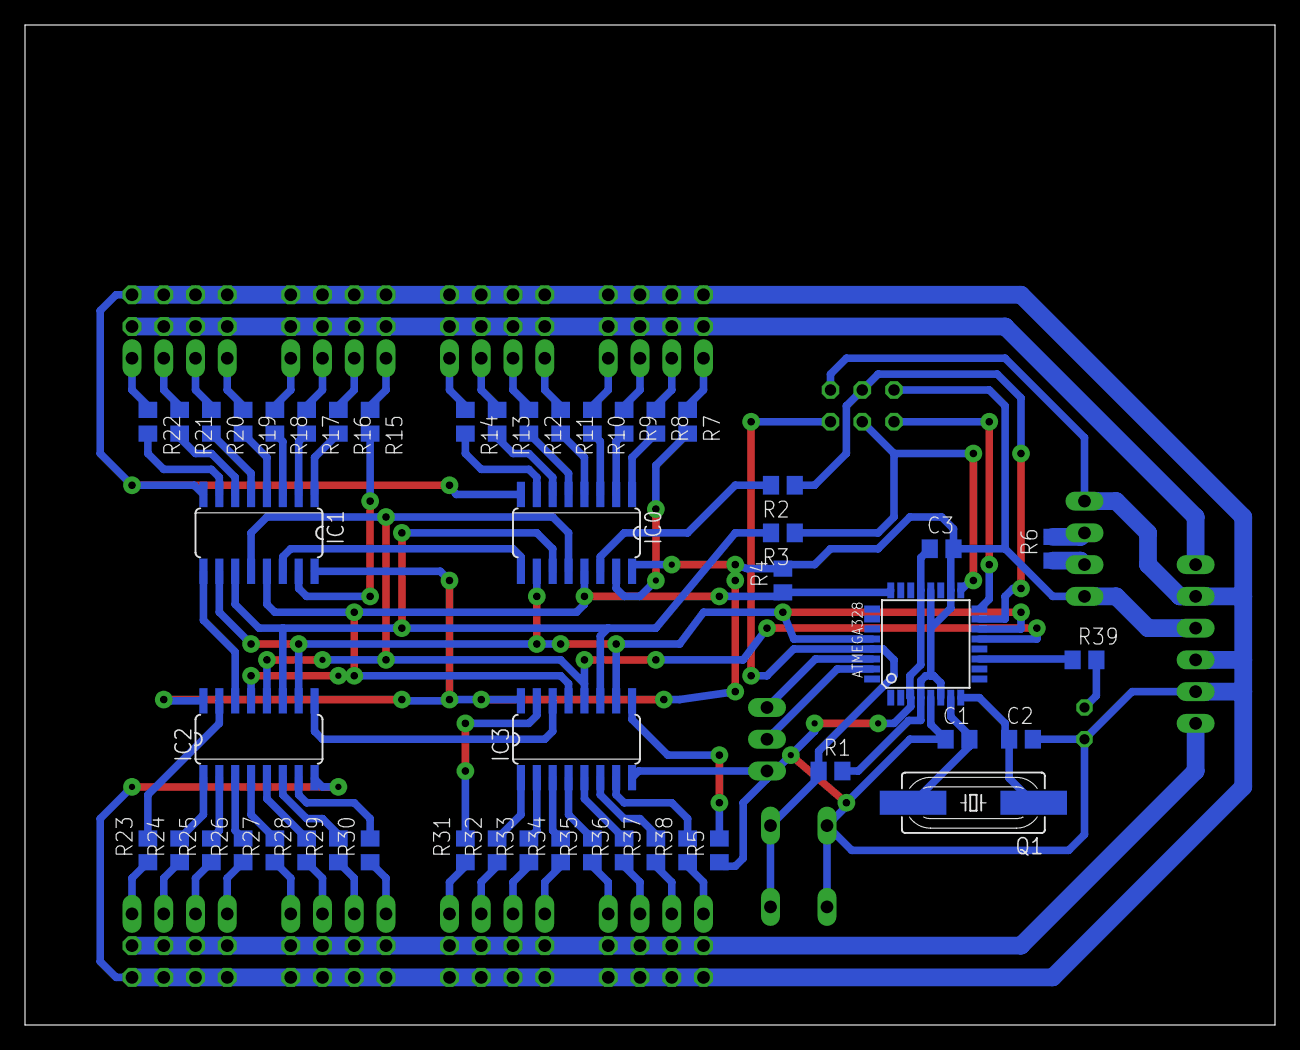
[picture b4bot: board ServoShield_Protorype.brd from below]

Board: 2 copper layers, 100.0 x 80.0 mm, 70 parts (48 on the bottom side), 89 nets.

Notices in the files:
parts and their libraries:
Wurth_Elektronik_Passive_rev15d: Copyright: Würth Elektronik
